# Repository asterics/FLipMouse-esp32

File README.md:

# FLipMouse goes ESP32

This repository contains the ongoing progress on the firmware for the FLipMouse version 3.
It will be API-compatible with FLipMouse v2, but with major improvements on speed (instead of one CortexM0 we will have a dual-core Tensilica and an additional CortexM0 for USB).

If you want to have a look at the FLipMouse v2, follow [this](https://github.com/asterics/FLipMouse) link to the main repository.

The BLE-HID stuff is based on the other [repository](https://github.com/asterics/esp32_mouse_keyboard), where we use the ESP32 as BLE module replacement.

Online demo version of Web GUI: https://asterics.github.io/FLipMouse-esp32/

__Following 3 steps are necessary to completely update/flash the firmware and the necessary support files/devices:__

## Building the ESP32 firmware

Please follow the step-by-step instructions of Espressif's ESP-IDF manual to setup the build infrastructure:
[Setup Toolchain](https://esp-idf.readthedocs.io/en/latest/get-started/index.html#setup-toolchain)

__Note:__ Due to frequent breaking changes within the esp-idf and all build tools, we recommend to use a specific version of the tools:
* release v4.1 (on 04.02.2020)
* master branch (on 04.02.2020)

To get this version, use the following commands:

  `git clone -b release/v4.1 --recursive https://github.com/espressif/esp-idf.git`  
  `cd esp-idf`  
  `./install.sh`  
  `. ./export.sh`  

																																																																																																																																																																																																																																																																																																																																																																																																																																																																																																																																																																																																																																																																																																																																																																																																																																																																																																																																																																																																																																																																																																																																																																																																																																																																																																																																																																																																																																																																																																																																																																																																																																																																																																																																																																																																																																																																																																																																																																																																																																																																																																																																																																																																												
__Now change your directory into the root directory of this repository.__

Create the sdkconfig:
* Execute `make menuconfig` in this directory
* Change: `Serial flasher config` -> `Flash size` to __4MB__
* Change: `Partition table` -> `Partition table` to __Custom partition table CSV__
* Change: `Component config` -> `Bluetooth` to enabled

Optional (for runtime statistics):
* Change: `Component config`->`FreeRTOS`->`Enable FreeRTOS trace facility` to enabled

Optional (extensive stack/heap debugging):
* Change `Component config`->`Heap memory debugging`->`Heap corruption detection` to whatever you need

After a successful setup, you should be able to build the FLipMouse/FABI firmware by executing 'make flash monitor'.

## Building the LPC11U14 firmware (USB bridging chip)

The dedicated USB chip firmware is located in this repository: [usb_bridge](https://github.com/benjaminaigner/usb_bridge/).
Please clone this repository, and import it into the MCUXpresso IDE.

You can download the IDE here:
[MCUXpresso IDE](http://www.nxp.com/mcuxpresso/ide)

After a successful build, you need to flash the firmware to the LPC11U14 chip. We recommend using a development board by Embedded Artists,
because it is very useful for initial testing & debugging. It is possible to split this board into two pieces, one LPC11U14 target and a JTAG
programmer, which we use on a fully assembled FLipMouse. Please refer to the corresponding documents of this board how to connect the JTAG header to
our FLipMouse (will be announced as soon as the PCB is final).

LPCXpresso development board:

[LPCXpresso 11U14](http://embeddedartists.com/products/lpcxpresso/lpc11U14_xpr.php)

## Uploading the WebGUI

The FLipMouse with ESP32 contains a web interface for customizing the parameters. The web page itself is located in the FAT partition as the config data.

-----------------------

TBA: I think it is very easy to use mkfats by copying the component into ESP-IDF and simply call **make mkfatfs** to build the tool and **make flashfatfs** to upload the image.

**BUT** we have a 8.3 naming convention here...

Currently proposed workflow:

-----------------------

Please clone/download the [mkfats](https://github.com/jkearins/ESP32_mkfatfs) tool, and copy the folder `ESP32_mkfatfs/components/mkfatfs` into your
ESP-IDF's components path.

Execute `make mkfatfs` in this repository to build the *mkfatfs* tool.

If you want to update the webpage on the FLipMouse/FABI device, execute:

`make makefatfs flashfatfs`

_WARNING:_** All your slot configuration and IR commands will be deleted by this operation.

## WARNING: THIS IS EARLY WORK IN PROGRESS

# Acknowledgements

Supporters, MA23, people using this device and many more for input.

ESP-IDF developers for HOG testcode

mkfatfs project

thanks to Luca Dentella for the esp32lights demo, see http://www.lucadentella.it/en/2018/01/08/esp32lights/

thanks to Jeroen Domburg and Cornelis for the captive portal DNS code, see: https://github.com/cornelis-61/esp32_Captdns

thanks to Thomas Barth for esp32 Websocket demo code, see https://github.com/ThomasBarth/WebSockets-on-the-ESP32/

thanks to Lucas Bruder for the Neopixel library for ESP32, see https://github.com/Lucas-Bruder/ESP32_LED_STRIP/

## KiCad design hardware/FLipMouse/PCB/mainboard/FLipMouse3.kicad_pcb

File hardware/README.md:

# FABI

This PCB is intended to be used with a **AK-S-01** case, produced by Szomk.

**Note:** This PCB was not produced yet, so no functional guarantee!

# FLipMouse 

This FLipMouse-esp32 PCB is tested by the *_PRE versions of the PCB.

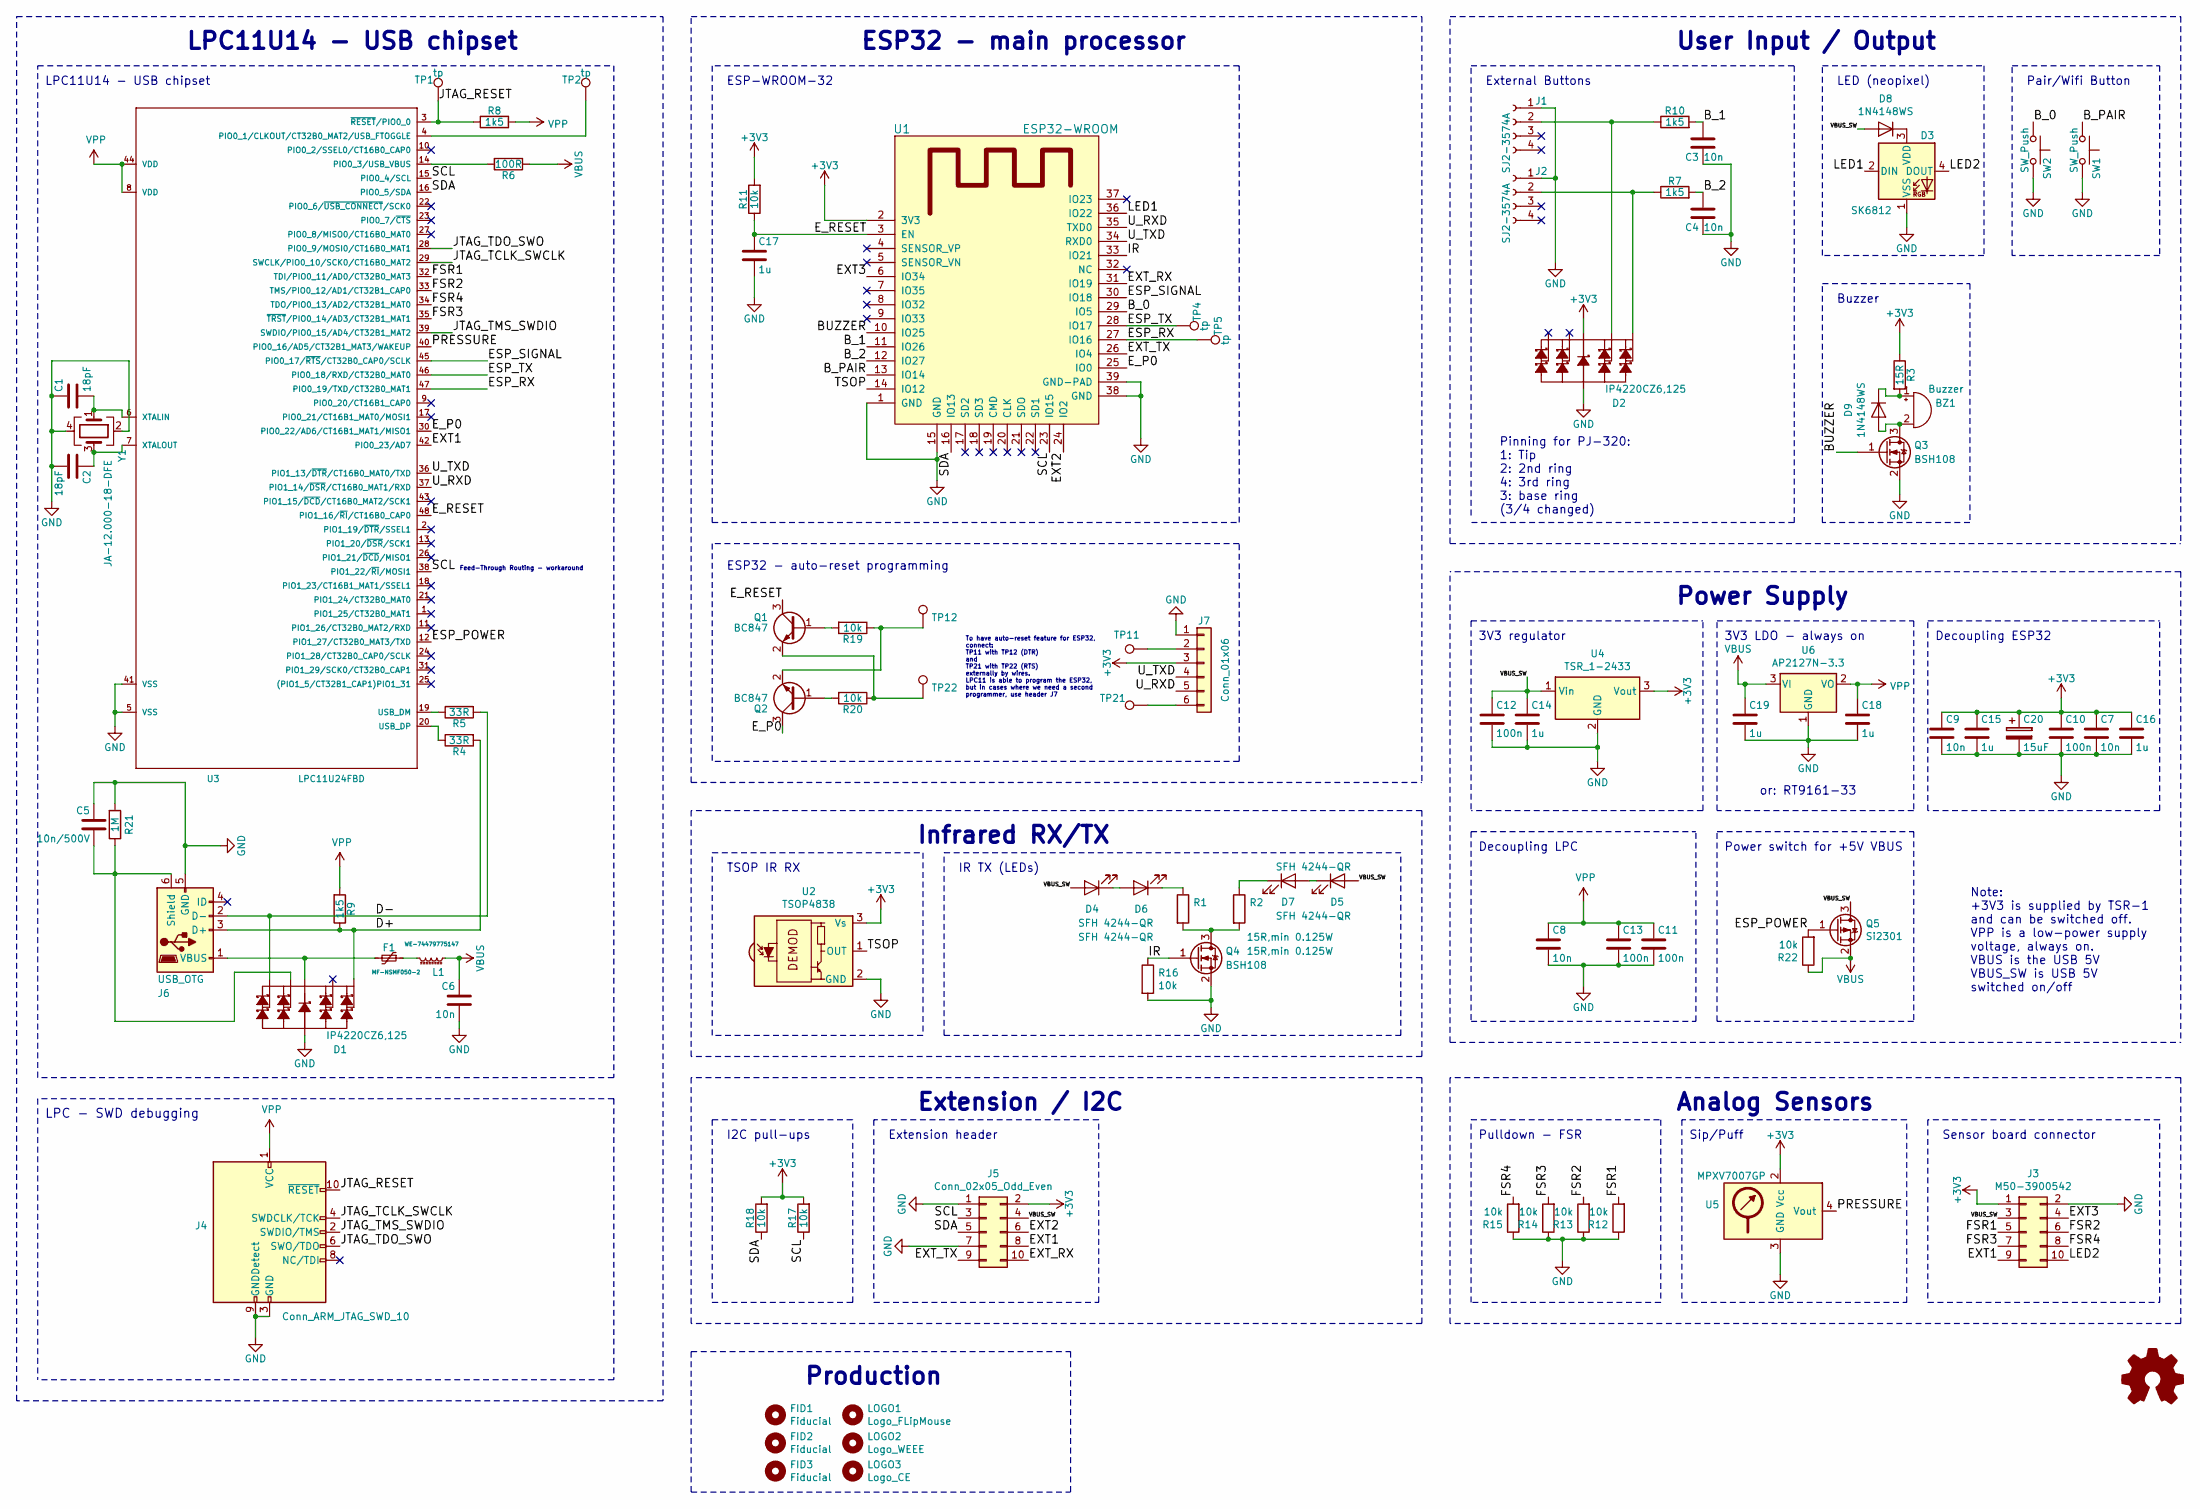
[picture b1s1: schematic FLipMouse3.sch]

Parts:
BZ1: Buzzer; MagneticBuzzer_Kingstate_KCG0601
C1, C2: 18pF; C_0603_1608Metric
C3, C4, C6, C7, C8, C9: 10n; C_0603_1608Metric
C5: 10n/500V; C_0603_1608Metric
C10, C11, C12, C13: 100n; C_0603_1608Metric
C14, C15, C16, C17, C18, C19: 1u; C_0805_2012Metric
C20: 15uF; CP_EIA-3216-18_Kemet-A
D1, D2: IP4220CZ6,125; SOT457
D3: SK6812; LED_SK6812_PLCC4_5.0x5.0mm_P3.2mm
D4, D5, D6, D7: SFH 4244-QR; SFH4244
D8, D9: 1N4148WS; D_SOD-323
F1: MF-NSMF050-2; C_1206_3216Metric
FID1, FID2, FID3: Fiducial; Fiducial_0.5mm_Dia_1mm_Outer
J1, J2: SJ2-3574A; Jack_3.5mm_SJ2-357X
J3: M50-3900542; PinHeader_2x05_P1.27mm_Horizontal
J4: Conn_ARM_JTAG_SWD_10; PinHeader_2x05_P1.27mm_Vertical_SMD
J5: Conn_02x05_Odd_Even; PinHeader_2x05_P1.27mm_Vertical_SMD
J6: USB_OTG; USB_Micro-B
J7: Conn_01x06; PinSocket_1x06_P1.27mm_Vertical
L1: WE-74479775147; L_0805_2012Metric
LOGO1: Logo_FLipMouse; flipmouse_11x5
LOGO2: Logo_WEEE; WEEE-Logo_4.2x6mm_SilkScreen
LOGO3: Logo_CE; CE
Q1, Q2: BC847; SOT-23
Q3, Q4: BSH108; SOT-23
Q5: Si2301; SOT-23
R1, R2: 15R,min 0.125W; R_0603_1608Metric
R3: 15R; R_0603_1608Metric
R4, R5: 33R; R_0603_1608Metric
R6: 100R; R_0603_1608Metric
R7, R8, R9, R10: 1k5; R_0603_1608Metric
R11, R12, R13, R14, R15, R16, R17, R18, R19, R20, R22: 10k; R_0603_1608Metric
R21: 1M; R_0603_1608Metric
SW1, SW2: SW_Push; SW_Tactile_SPST_Angled_PTS645Vx83-2LFS
TP1, TP2, TP4, TP5: tp; Measurement_Point_Round-SMD-Pad_Small
TP11, TP12, TP21, TP22: TP; TestPoint_Pad_D1.0mm
U1: ESP32-WROOM
U2: TSOP4838; Vishay_MOLD-3Pin
U3: LPC11U24FBD; LQFP-48_7x7mm_P0.5mm
U4: TSR_1-2433; Converter_DCDC_TRACO_TSR-1_THT
U5: MPXV7007GP
U6: AP2127N-3.3; SOT-23
Y1: JA-12.000-18-DFE; Crystal_SMD_3225-4Pin_3.2x2.5mm

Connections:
+3V3: C7.1, C9.1, C10.1, C15.1, C16.1, C20.1, D2.5 (VCC), J3.1, J5.2, J7.3, R3.1, R11.2, R17.2, R18.2, U1.2 (3V3), U2.3 (Vs), U4.3 (Vout), U5.2 (Vcc)
/BUZZER: Q3.1 (G), U1.10 (IO25)
/B_0: SW2.1, U1.29 (IO5)
/B_1: C3.2, R10.2, U1.11 (IO26)
/B_2: C4.2, R7.2, U1.12 (IO27)
/B_PAIR: SW1.1, U1.13 (IO14)
/D+: D1.6 (IO), J6.3 (D+), R4.2, R9.1
/D-: D1.1 (IO), J6.2 (D-), R5.2
/ESP_POWER: Q5.1 (G), R22.2, U3.12 (PIO1_27/CT32B0_MAT3/TXD)
/ESP_RX: TP5.1, U1.27 (IO16), U3.47 (PIO0_19/TXD/CT32B0_MAT1)
/ESP_SIGNAL: U1.30 (IO18), U3.45 (PIO0_17/~RTS~/CT32B0_CAP0/SCLK)
/ESP_TX: TP4.1, U1.28 (IO17), U3.46 (PIO0_18/RXD/CT32B0_MAT0)
/EXT1: J3.9, J5.8, U3.42 (PIO0_23/AD7)
/EXT2: J5.6, U1.24 (IO2)
/EXT3: J3.4, U1.6 (IO34)
/EXT_RX: J5.10, U1.31 (IO19)
/EXT_TX: J5.9, U1.26 (IO4)
/E_P0: Q2.3 (C), U1.25 (IO0), U3.30 (PIO0_22/AD6/CT16B1_MAT1/MISO1)
/E_RESET: C17.1, Q1.3 (C), R11.1, U1.3 (EN), U3.48 (PIO1_16/~RI~/CT16B0_CAP0)
/FSR1: J3.5, R12.2, U3.32 (TDI/PIO0_11/AD0/CT32B0_MAT3)
/FSR2: J3.6, R13.2, U3.33 (TMS/PIO0_12/AD1/CT32B1_CAP0)
/FSR3: J3.7, R14.2, U3.35 (~TRST~/PIO0_14/AD3/CT32B1_MAT1)
/FSR4: J3.8, R15.2, U3.34 (TDO/PIO0_13/AD2/CT32B1_MAT0)
/IR: Q4.1 (G), R16.1, U1.33 (IO21)
/JTAG_RESET: J4.10 (~RESET~), R8.1, TP1.1, U3.3 (~RESET~/PIO0_0)
/JTAG_TCLK_SWCLK: J4.4 (SWDCLK/TCK), U3.29 (SWCLK/PIO0_10/SCK0/CT16B0_MAT2)
/JTAG_TDO_SWO: J4.6 (SWO/TDO), U3.28 (PIO0_9/MOSI0/CT16B0_MAT1)
/JTAG_TMS_SWDIO: J4.2 (SWDIO/TMS), U3.39 (SWDIO/PIO0_15/AD4/CT32B1_MAT2)
/LED1: D3.2 (DIN), U1.36 (IO22)
/LED2: D3.4 (DOUT), J3.10
/PRESSURE: U3.40 (PIO0_16/AD5/CT32B1_MAT3/WAKEUP), U5.4 (Vout)
/SCL: J5.3, R17.1, U1.23 (IO15), U3.15 (PIO0_4/SCL), U3.38 (PIO1_22/~RI~/MOSI1)
/SDA: J5.5, R18.1, U1.16 (IO13), U3.16 (PIO0_5/SDA)
/TSOP: U1.14 (IO12), U2.1 (OUT)
/U_RXD: J7.5, U1.35 (TXD0), U3.37 (PIO1_14/~DSR~/CT16B0_MAT1/RXD)
/U_TXD: J7.4, U1.34 (RXD0), U3.36 (PIO1_13/~DTR~/CT16B0_MAT0/TXD)
/VBUS_SW: C12.1, C14.1, D4.2 (A), D5.2 (A), D8.2 (A), J3.3, J5.4, Q5.3 (D), U4.1 (Vin)
GND: C1.1, C2.2, C3.1, C4.1, C5.1, C6.2, C7.2, C8.2, C9.2, C10.2, C11.2, C12.2, C13.2, C14.2, C15.2, C16.2, C17.2, C18.2, C19.2, C20.2, D1.2 (GND), D2.2 (GND), D3.1 (VSS), J1.1, J2.1, J3.2, J4.3 (GND), J4.5 (GND), J4.9 (GNDDetect), J5.1, J5.7, J6.5 (GND), J7.1, Q3.2 (S), Q4.2 (S), R12.1, R13.1, R14.1, R15.1, R16.2, R21.2, SW1.2, SW2.2, U1.1 (GND), U1.15 (GND), U1.38 (GND), U1.39 (GND-PAD), U2.2 (GND), U3.5 (VSS), U3.41 (VSS), U4.2 (GND), U5.3 (GND), U6.1 (GND), Y1.2, Y1.4
unnamed: BZ1.1 (-), D9.1 (K), R3.2
unnamed: BZ1.2 (+), D9.2 (A), Q3.3 (D)
unnamed: C1.2, U3.6 (XTALIN), Y1.1
unnamed: C2.1, U3.7 (XTALOUT), Y1.3
unnamed: C5.2, D1.3 (IO), J6.6 (Shield), R21.1
unnamed: D1.5 (VCC), F1.2, J6.1 (VBUS)
unnamed: D2.4 (IO), J1.2, R10.1
unnamed: D2.6 (IO), J2.2, R7.1
unnamed: D3.3 (VDD), D8.1 (K)
unnamed: D4.1 (K), D6.2 (A)
unnamed: D5.1 (K), D7.2 (A)
unnamed: D6.1 (K), R1.1
unnamed: D7.1 (K), R2.1
unnamed: F1.1, L1.1
unnamed: J7.2, TP11.1
unnamed: J7.6, TP21.1
unnamed: Q1.1 (B), R19.2
unnamed: Q1.2 (E), R20.1, TP22.1
unnamed: Q2.1 (B), R20.2
unnamed: Q2.2 (E), R19.1, TP12.1
unnamed: Q4.3 (D), R1.2, R2.2
unnamed: R4.1, U3.20 (USB_DP)
unnamed: R5.1, U3.19 (USB_DM)
unnamed: R6.2, U3.14 (PIO0_3/USB_VBUS)
unnamed: TP2.1, U3.4 (PIO0_1/CLKOUT/CT32B0_MAT2/USB_FTOGGLE)
VBUS: C6.1, C19.1, L1.2, Q5.2 (S), R6.1, R22.1, U6.3 (VI)
VPP: C8.1, C11.1, C13.1, C18.1, J4.1 (VCC), R8.2, R9.2, U3.8 (VDD), U3.44 (VDD), U6.2 (VO)

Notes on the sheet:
Pair/Wifi Button
Buzzer
LED (neopixel)
Pinning for PJ-320: 1: Tip 2: 2nd ring 4: 3rd ring 3: base ring (3/4 changed)
LPC11U14 - USB chipset
Decoupling ESP32
External Buttons
ESP32 - auto-reset programming
LPC - SWD debugging
ESP-WROOM-32
User Input / Output
Power Supply
3V3 regulator
Decoupling LPC
Analog Sensors
Pulldown - FSR
Sip/Puff
Sensor board connector
Extension / I2C
I2C pull-ups
Extension header
ESP32 - main processor
Infrared RX/TX
TSOP IR RX
IR TX (LEDs)
Production
To have auto-reset feature for ESP32, connect: TP11 with TP12 (DTR) and TP21 with TP22 (RTS) externally by wires. LPC11 is able to program the ESP32, but in cases where we need a second programmer, use header J7
Feed-Through Routing - workaround
Note: +3V3 is supplied by TSR-1 and can be switched off. VPP is a low-power supply voltage, always on. VBUS is the USB 5V VBUS_SW is USB 5V switched on/off
or: RT9161-33
3V3 LDO - always on
Power switch for +5V VBUS

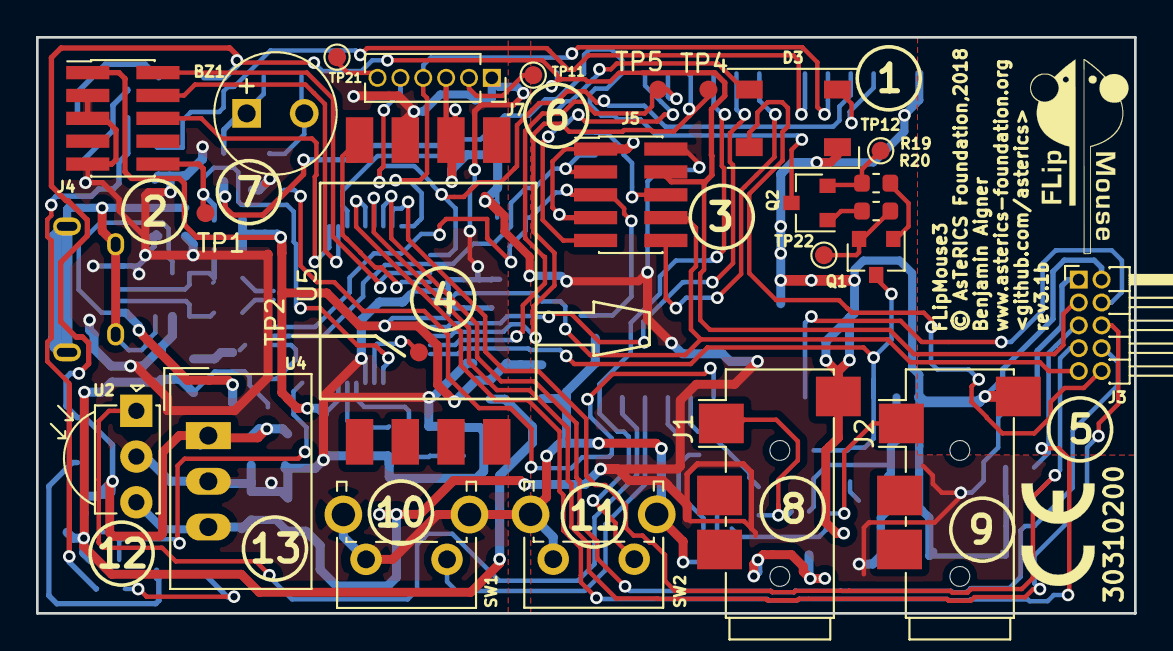
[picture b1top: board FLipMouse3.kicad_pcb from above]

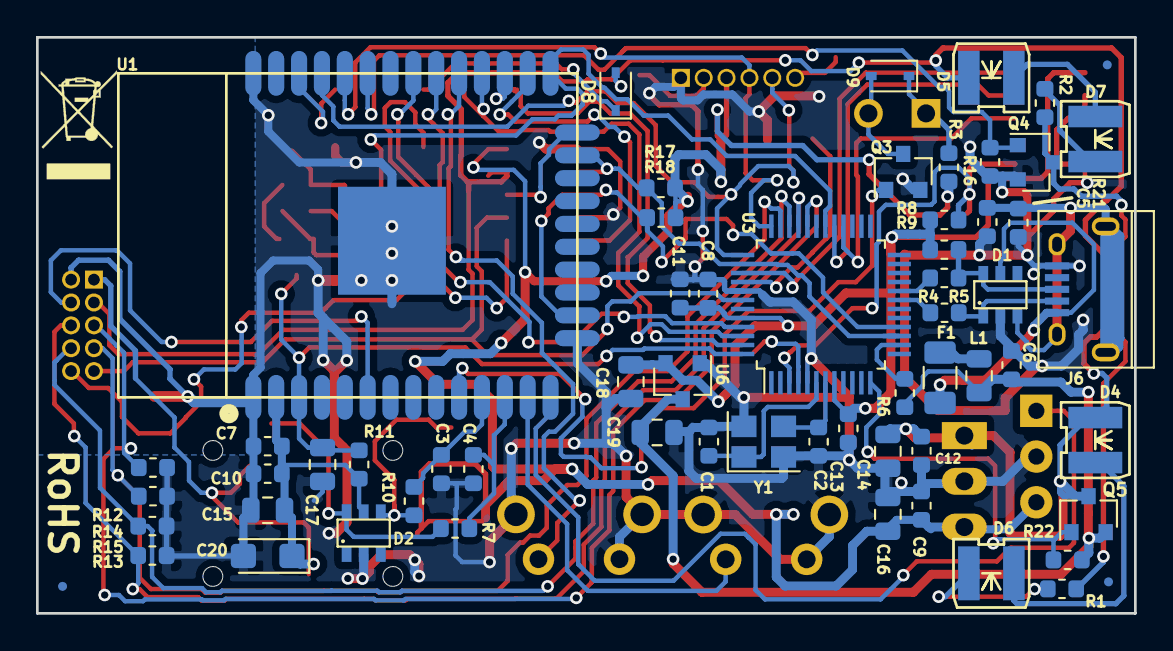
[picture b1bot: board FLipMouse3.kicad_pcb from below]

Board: 2 copper layers, 61.0 x 32.0 mm, 89 parts (62 on the bottom side), 65 nets.

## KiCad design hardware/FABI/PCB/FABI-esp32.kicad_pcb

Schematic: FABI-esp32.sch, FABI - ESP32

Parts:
BZ1: Buzzer; MagneticBuzzer_Kingstate_KCG0601
C1, C2: 18pF; C_0603_1608Metric
C3, C4, C5, C6, C7, C8, C9, C10, C12, C13, C14: 10n; C_0603_1608Metric
C11: 10n/500V; C_0603_1608Metric
C15, C16, C17, C18: 100n; C_0603_1608Metric
C19, C20, C21, C22: 1u; C_0805_2012Metric
C23: 15uF; CP_EIA-3216-18_Kemet-A
D1, D2, D3, D4: IP4220CZ6,125; SOT457
D5: 1N4148WS; D_SOD-323
D6: SK6812; LED_SK6812_PLCC4_5.0x5.0mm_P3.2mm
F1: MF-NSMF050-2; C_1206_3216Metric
FID1, FID2, FID3: Fiducial; Fiducial_0.5mm_Dia_1mm_Outer
J1, J2, J3, J4, J5, J6, J7, J8: SJ2-3574A; Jack_3.5mm_SJ2-357X
J9: USB_OTG; USB_Micro-B
J10: Conn_01x04; PinSocket_1x04_P2.54mm_Vertical
J11: Conn_01x06; PinHeader_1x06_P2.54mm_Vertical
J12: Conn_01x08_Male; PinHeader_1x08_P2.54mm_Vertical
J13, J14, J15, J16, J17: tp; TestPoint_Pad_D1.0mm
L1: WE-74479775147; L_0805_2012Metric
LOGO1: LOGO_CE; CE
LOGO2, LOGO4: LOGO_FABI; fabi_15x8
LOGO3: LOGO_WEEE; WEEE-Logo_4.2x6mm_SilkScreen
MH1, MH2, MH3, MH4: TEST; MountingHole_4.5mm_wo_crtyd
Q1, Q2: BC847; SOT-23
Q3, Q4, Q5: BSH108; SOT-23
R1, R2: 33R; R_0603_1608Metric
R3, R4: 100R; R_0603_1608Metric
R5, R6, R7, R8, R9, R10, R14: 1.5k; R_0603_1608Metric
R11, R12, R13: 1k5; R_0603_1608Metric
R15, R16, R17, R18, R19, R20: 10k; R_0603_1608Metric
R21: 1M; R_0603_1608Metric
SW1: SW_Push; SW_Tactile_SPST_Angled_PTS645Vx83-2LFS
U1: ESP32-WROOM
U2: TSR_1-2433; Converter_DCDC_TRACO_TSR-1_THT
U3: LPC11U14FBD; LQFP-48_7x7mm_P0.5mm
Y1: JA-12.000-18-DFE; Crystal_SMD_3225-4Pin_3.2x2.5mm

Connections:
+3V3: C12.1, C13.1, C14.1, C15.1, C16.1, C17.1, C19.1, C22.1, C23.1, D1.5 (VCC), D2.5 (VCC), D3.4 (IO), D3.5 (VCC), J8.2, J10.2, J11.3, J12.1, R11.1, R12.2, R13.2, R17.2, R18.2, R20.2, U1.2 (3V3), U2.3 (Vout), U3.8 (VDD), U3.44 (VDD)
/BUZZER: Q3.1 (G), U1.12 (IO27)
/B_0: C6.2, R14.2, U1.4 (SENSOR_VP)
/B_1: C8.2, R8.2, U1.5 (SENSOR_VN)
/B_2: C3.2, R5.2, U1.8 (IO32)
/B_3: C4.2, R6.2, U1.9 (IO33)
/B_4: C5.2, R7.2, U1.10 (IO25)
/B_5: C7.2, R9.2, U1.11 (IO26)
/B_6: C9.2, R10.2, U1.13 (IO14)
/B_PAIR: SW1.1, U1.37 (IO23)
/D+: D4.6 (IO), J9.3 (D+), R2.2, R13.1
/D-: D4.1 (IO), J9.2 (D-), R1.2
/DD+: R2.1, U3.20 (USB_DP)
/DD-: R1.1, U3.19 (USB_DM)
/ESP_POWER: Q5.1 (G), U3.27 (PIO0_8/MISO0/CT16B0_MAT0)
/ESP_RX: J17.1, U1.27 (IO16), U3.47 (PIO0_19/TXD/CT32B0_MAT1)
/ESP_SIGNAL: U1.30 (IO18), U3.45 (PIO0_17/~RTS~/CT32B0_CAP0/SCLK)
/ESP_TX: J16.1, U1.28 (IO17), U3.46 (PIO0_18/RXD/CT32B0_MAT0)
/E_P0: Q2.3 (C), U1.25 (IO0)
/E_RESET: C21.1, Q1.3 (C), R20.1, U1.3 (EN)
/IR: Q4.1 (G), R15.2, U1.31 (IO19)
/JTAG_RESET: J12.6, J13.1, R12.1, U3.3 (~RESET~/PIO0_0)
/JTAG_TCLK_SWCLK: J12.3, U3.29 (SWCLK/PIO0_10/SCK0/CT16B0_MAT2)
/JTAG_TDO_SWO: J12.4, U3.28 (PIO0_9/MOSI0/CT16B0_MAT1)
/JTAG_TMS_SWDIO: J12.2, U3.39 (SWDIO/PIO0_15/AD4/CT32B1_MAT2)
/LED1: D6.2 (DIN), U1.36 (IO22)
/SCL: J10.4, R18.1, U1.23 (IO15), U3.15 (PIO0_4/SCL)
/SDA: J10.3, R17.1, U1.16 (IO13), U3.16 (PIO0_5/SDA)
/TSOP: R4.1, U1.7 (IO35)
/U_RXD: J11.5, U1.35 (TXD0)
/U_TXD: J11.4, U1.34 (RXD0)
GND: C1.1, C2.2, C10.2, C11.1, C13.2, C14.2, C15.2, C16.2, C18.2, C19.2, C20.2, D4.2 (GND), J9.5 (GND), J12.8, Q5.2 (S), R21.2, U2.2 (GND), U3.5 (VSS), U3.41 (VSS), Y1.2, Y1.4
GNDD: C3.1, C4.1, C5.1, C6.1, C7.1, C8.1, C9.1, C12.2, C17.2, C21.2, C22.2, C23.2, D1.2 (GND), D2.1 (IO), D2.2 (GND), D3.2 (GND), D3.3 (IO), D6.1 (VSS), J1.1, J2.1, J3.1, J4.1, J5.1, J6.1, J7.1, J8.4, J10.1, J11.1, Q3.2 (S), Q4.2 (S), Q5.3 (D), R15.1, SW1.2, U1.1 (GND), U1.15 (GND), U1.38 (GND), U1.39 (GND-PAD)
unnamed: BZ1.1 (-), R11.2
unnamed: BZ1.2 (+), Q3.3 (D)
unnamed: C1.2, U3.6 (XTALIN), Y1.1
unnamed: C2.1, U3.7 (XTALOUT), Y1.3
unnamed: C11.2, D4.4 (IO), J9.6 (Shield), R21.1
unnamed: D1.1 (IO), J3.2, R5.1
unnamed: D1.3 (IO), J4.2, R6.1
unnamed: D1.4 (IO), J2.2, R8.1
unnamed: D1.6 (IO), J1.2, R14.1
unnamed: D2.3 (IO), J7.2, R10.1
unnamed: D2.4 (IO), J6.2, R9.1
unnamed: D2.6 (IO), J5.2, R7.1
unnamed: D3.1 (IO), J8.3, Q4.3 (D)
unnamed: D3.6 (IO), J8.1, R4.2
unnamed: D4.5 (VCC), F1.2, J9.1 (VBUS)
unnamed: D5.1 (K), D6.3 (VDD)
unnamed: F1.1, L1.1
unnamed: J11.2, Q2.2 (E), R19.1
unnamed: J11.6, Q1.2 (E), R16.1
unnamed: J14.1, U3.4 (PIO0_1/CLKOUT/CT32B0_MAT2/USB_FTOGGLE)
unnamed: J15.1, R3.2, U3.14 (PIO0_3/USB_VBUS)
unnamed: Q1.1 (B), R19.2
unnamed: Q2.1 (B), R16.2
VBUS: C10.1, C18.1, C20.1, D5.2 (A), L1.2, R3.1, U2.1 (Vin)

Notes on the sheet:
Pair/Wifi Button
Buzzer
LED (neopixel)
LPC11U14 - USB chipset
Decoupling for LPC & ESP32
IR+TSOP external Jackplug
7x external Jackplugs
3V3 regulator + power switch for ESP32
Designed like ESP32 Thing (Sparkfun)
Programming interfaces
ESP-WROOM-32
I2C (display or ext)
Mounting holes
Note: to have 3v3 compatible SK6812, we need to reduce the supply voltage: 5V-0,7V->4,3V*0,7->Din(high,min) = 3V
Microcontrollers
User I/O
Power
Production
Infrared (external)
USB compatible interface
Logos
Fiducials

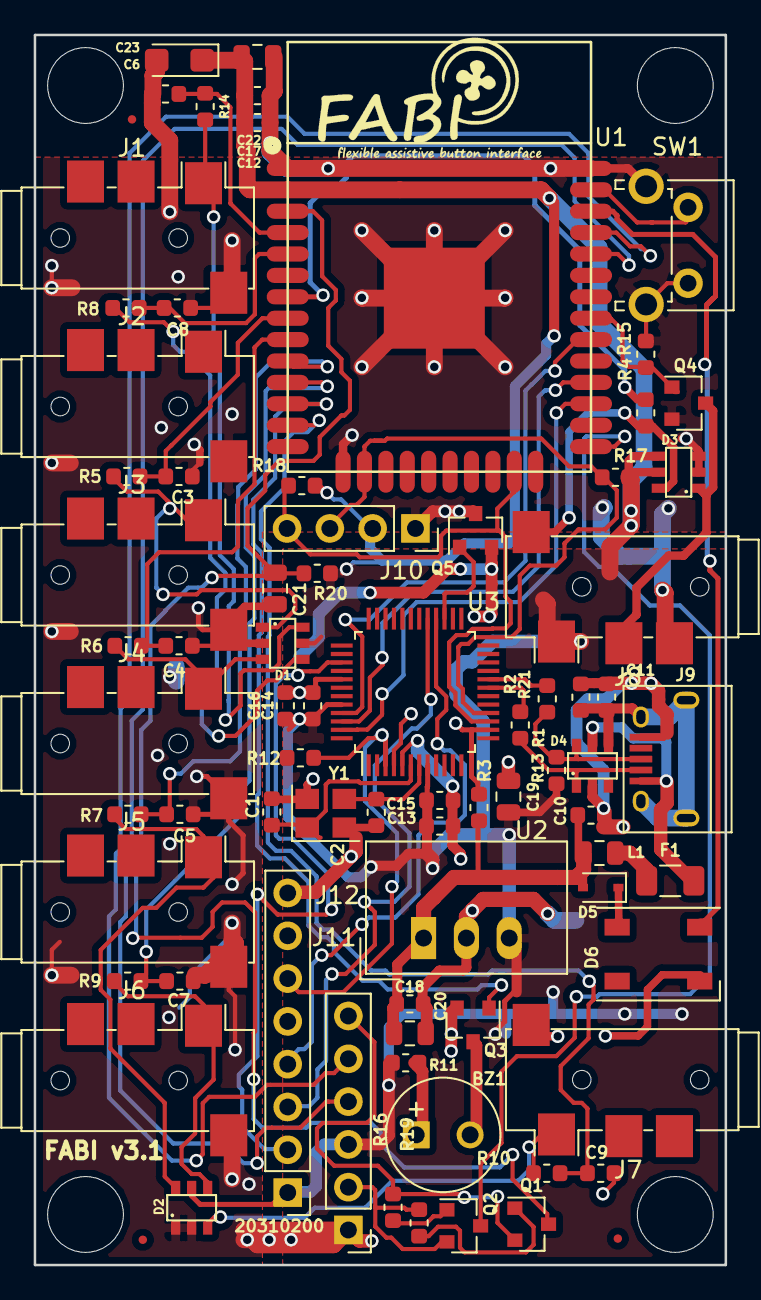
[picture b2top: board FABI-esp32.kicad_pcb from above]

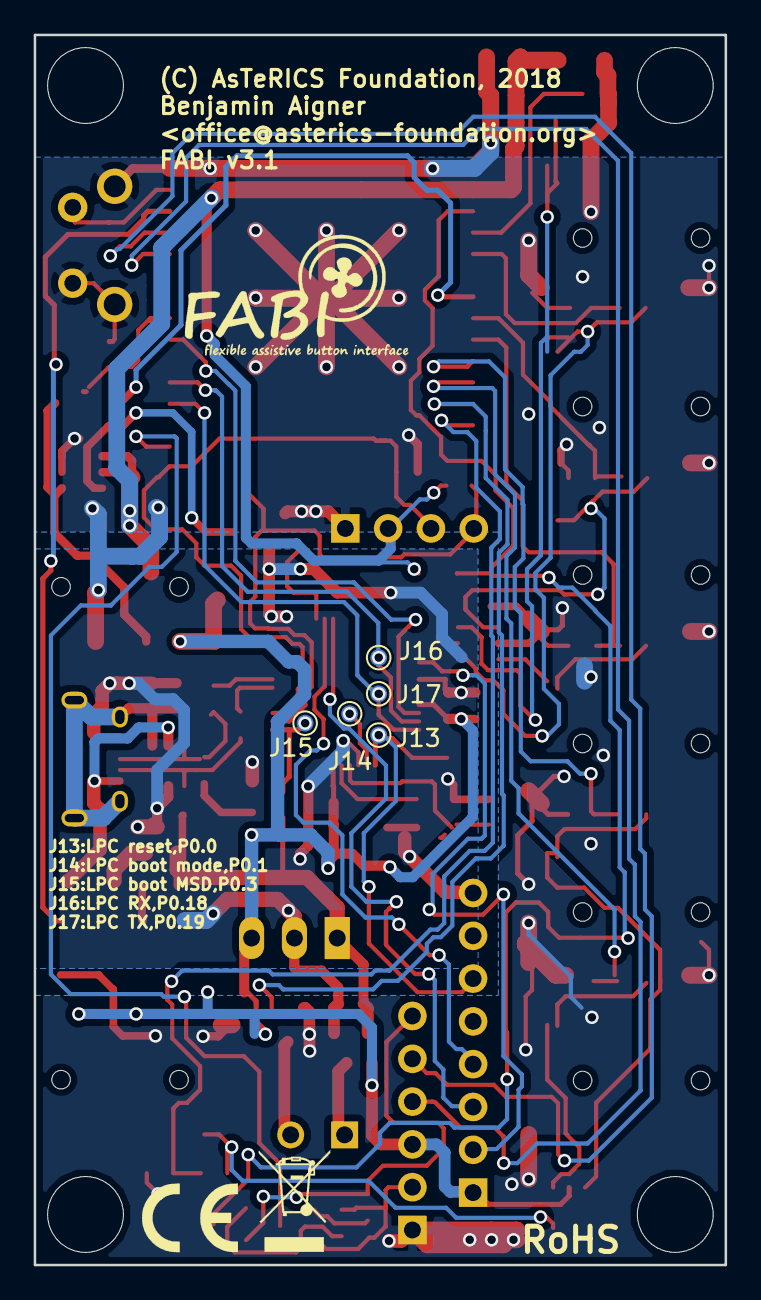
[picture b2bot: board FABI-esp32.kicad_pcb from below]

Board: 2 copper layers, 41.0 x 73.0 mm, 91 parts (8 on the bottom side), 57 nets.

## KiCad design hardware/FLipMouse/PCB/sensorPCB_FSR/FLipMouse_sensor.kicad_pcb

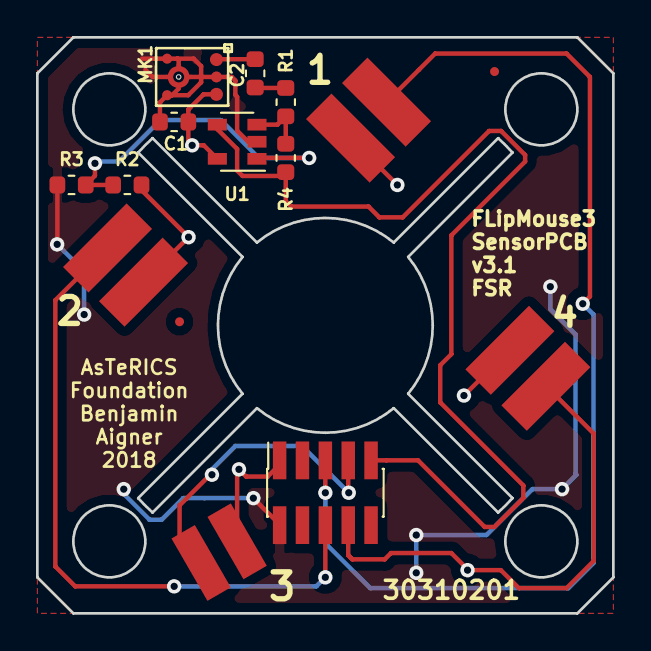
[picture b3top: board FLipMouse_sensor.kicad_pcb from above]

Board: 2 copper layers, 32.0 x 32.0 mm, 19 parts (0 on the bottom side), 11 nets.

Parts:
C1: 100nF; C_0603_1608Metric
C2: 4.7uF; C_0603_1608Metric
FID1, FID2: Fiducial; Fiducial_0.5mm_Dia_1mm_Outer
J1: Conn_02x05_Odd_Even; PinSocket_2x05_P1.27mm_Vertical_SMD
J2, J3: FSR1; FSRPAD
J4, J5: FSR2; FSRPAD
J6, J7: FSR3; FSRPAD
J8, J9: FSR4; FSRPAD
MK1: SPU0410LR5H; SPU0410LR5H_6_3.76x3mm
R1: 10k; R_0603_1608Metric
R2, R3, R4: 100k; R_0603_1608Metric
U1: LMV321; SOT-23-5

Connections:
3V3: C1.1, J1.1, J3.1, J5.1, J7.1, J9.1, MK1.4, R2.2, U1.5
/1: J1.5, J2.1
/2: J1.6, J4.1
/3: J1.7, J6.1
/4: J1.8, J8.1
/EXT1: J1.9, R4.1, U1.4
GNDD: C1.2, J1.2, MK1.2, MK1.3, MK1.5, MK1.6, R3.1, U1.2
unnamed: C2.1, R1.2
unnamed: C2.2, MK1.1
unnamed: R1.1, R4.2, U1.3
unnamed: R2.1, R3.2, U1.1

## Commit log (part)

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2018-05-03 changed colors in order to meet aria contrast criteria
2018-05-03 added translations for "connected" and "not connected"
2018-05-03 added classes for displaying items only for screenreaders and for connection indicators
2018-05-04 changed access keys of sip/puff sliders because alt+e is chrome menu
2018-05-06 Added mode for strong sip/puff
2018-05-06 Added conditions for strong mode + XX in tasks, handling tbd
2018-05-09 Reduced priority of tasks for kbd/mouse/joystick & set baudrate to 115200
2018-05-12 Added a check for current BT status, avoiding errors on re-enabling
2018-05-12 Added compatibility flag
2018-05-12 Starting with slot number 0, not having a "special", not removable slot.
2018-05-12 Added v2.5. note on AT LA/ AT DE
2018-05-12 Put LED update into the macro instead of a task (Neopixel still need a task)
2018-05-16 Fixed heap corruption with reduced buffers
2018-05-21 Changed task priority of config switcher, removed NL characters from ID string
2018-05-21 Added opening partition, to be save if webgui is initialized before storage
2018-05-21 Starting with slot 0, no "DEFAULT" slot
2018-05-21 Changed RMT blocks to 3, on all occasions, freeing one for Neopixels and one for HID output
2018-05-22 Added declaration for queue & usb command
2018-05-23 Added note on slot 0
2018-05-23 Changed for new HID sending
2018-05-23 Added "END" after sending a slot
2018-05-23 Changed storage for slot 0 and -1 for delete all, added note. AT LA bugfix, sending "END" at the end
2018-05-24 Updated documentation & changed loglevel for USB mouse to DEBUG
2018-05-24 Fixed corrupted slots on save due to not-synchronized config data
2018-05-24 Extended data output for saving slots (deactivated by #if 0)
2018-05-28 Removed espressif BLE stuff, added Nkolban's BLE stack
2018-05-28 Improved&simplified calibration:
    - Using same adc read function
    - Removing problem with sensor gain (was not take into account for calibration)
2018-05-28 implemented queue parsing
2018-05-28 BLE/WiFi switch without pairing (is normally active if no device is connected)
2018-05-28 Changed AT BM numbering
2018-05-29 Added sip/puff calibration. Sometimes the 5V type has a significant offset, is calibrated now
2018-05-29 Reduced debug output, controllable via LOG_LEVEL_STORAGE define
2018-05-29 Moved radio switch to main task, reducing stack load on timer
2018-05-29 Reduced main stack size, fixed error on switching off wifi
2018-05-30 Changed stacksize to 8k, replaced printf by ESP_LOGx
2018-05-30 Activated BT/Wifi coexistance, don't know if it helps...
2018-06-04 Changed error checks for getting wifi station count, added guards for wifi deinit
2018-06-04 Doxygen docs updated to current status
2018-06-13 Changed individual tasks to task_hid
2018-06-13 Added HID task
2018-06-13 Added store/load for HID command chain
2018-06-13 Rewrote parser for short HID commands
2018-06-21 Removed now unused kbd/mouse tasks -> moved to task_hid
2018-06-21 Changed comments -> HID task is continous, not functional.
2018-06-21 Changed further to use simple VB task
2018-07-24 Changed sdkconfig & websocket file for esp-idf release v3.1
2018-08-03 Renamed default file to flip.set (allowing a default fabi.set)
2018-08-06 Changed load function to use AT commands from files.
2018-08-07 Major improvements/fixes:
    - Fixed AT AY command
    - Fixing buffer errors on AT SS/AT SP
    - Moved slot storing to an individual function (refactored old printAll function -> now storing AT commands in flash)
    - Slot printing is now mostly done in hal_storage (because the output of "AT LA" is already stored in flash)
2018-08-07 Major improvements:
    - Added a stripping function to remove \r\n
    - Changed config names from 000.fms to 000.set
    - Added serial output to halStorageLoadNumber -> replacing the printAll function from task_commands
    - Added a global file handle for a session, allow appending lines on each call of halStorageStore (less memory for saving AT command lines)
    - Removed all VB/HID chain store/load functions
2018-08-07 Implemented "AT NE" by sending command chain parameter to config switcher queue
2018-08-07 Added breaks for command type detection
2018-08-13 DOXY: Typos, Todos
2018-08-14 OTF calibration, not activated now (missing good values from normal sensors)
2018-10-10 Changed component names for having all part types in one order. Added 3d shapes & beautified silkscreen layers.
2018-10-15 Added requirementsspecification for FABI3 (necessary for certification)
2018-11-15 Production ready, alpha: * Added marks/logos/fiducials * Changed neopixel driving * Moved RX/TX of EXT header from internal UART to free pins * Renumbered all parts for having same part types with fo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
2018-11-21 Checklist: removed EdgeCut layer from single page PCB print Added the update of the 3D renderings
2018-11-21 Improvements&fixes: * Replaced PJ320D (china jack plugs) with plugs from digikey (RoHS!) * Added remaining 3D shapes to PCB * Removed GND from unused jack plug pins (might result in unusable buttons 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
2018-11-25 Pin config update for FABI, removed OTF calibration via defines for FABI
2018-11-25 Added kicad backup files to gitignore, added FABI rescue lib
2018-12-02 Updated FLipMouse PCB: - Routed ADC inputs (FSR+pressure) to LPC11 too (in case of crappy ESP ADC values) - Added ESP32 auto-reset pins to LPC11 (enabling programming via LPC USB) - Cleanup regarding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
2019-01-07 Added function to check if 'sip and puff' is available
2019-01-29 Added default files for FLipMouse configs. Removed gain settings
2019-01-29 Small documentation updates. Fixed R10, according to batch documentation (batch 'a'), from 1k5 to 15R (series resistor for buzzer)
2019-02-05 Clearing empty command queue flag before loading slots. Changed debug level to info
2019-02-05 Changed to use new parser:
    -) Commands are defined now in structure
    -) Parser is based on: https://gitlab.com/ba.1150/cmd_parser_esp32
    -) Parser modifies either the generalConfig_t struct OR calls a handler
2019-02-05 Changed LED number if WiFi is active (now it is purple)
2019-02-05 Added debug output for command chain.
2019-02-05 remove newline
2019-02-06 Keycode parser using parameter, not full string. Added debug output for press action.
2019-02-07 Changed version string to v2.7 (compatible with FlipMouseGUI)
2019-02-08 Updated sdkconfig to esp idf release v3.2
2019-02-08 Changed wifi/ble switching: -) BLE is always active -) BLE/Wifi co-existance is done in esp-idf -) Wifi is switched on/off by the special button handler
2019-02-09 Added detailed debouncer output; added printf macros for printing single bits
2019-02-09 Replaced the out event flags (signalling to task_hid, task_vb) by an event loop:
    -) renamed task_hid / task_vb to handler_hid/handler_vb
    -) Deleted virtualButtonsOut event group
    -) Removed task structure, replaced by event handler
    -) Changed functions in all calling modules
2019-02-12 Fixed wrong IR file numbering -> could play, delete but not storing more than one IR command.
2019-02-13 Debouncer has highest priority.
2019-02-13 Fixed AT K* commands: press/release flags were wrong Cleaned up deboug output
2019-02-13 Fixed wrong press/release assignment for keyboard actions; removed trailing \r\n characters
2019-02-13 Fixed check for slot number (do this only on creating a new slot)
2019-03-08 Small comment updates; changed default slot settings
2019-03-11 ADC measurements via LPC - I2C communication for data
2019-03-11 Unified 3V3 (switched), according to chapter 9.4 of LPC datasheet, the high power pin doesn't deliver 3v3.
2019-03-13 Added an output for parsing errors.
2019-03-13 Changed log output to level info
2019-03-13 Changed SPIFFS script, modified sdkconfig to use same SPIFFS settings as mkspiffs in standard configuration
2019-03-15 UPdates in tone creation, queue was too short for e.g. slot nr 5 beeps.
2019-03-15 Disabled elliptic deadzone, can be enabled by define
2019-03-15 Fixed missing X+Y axis mouse command (was only active for a single axis).
2019-03-18 Moved BLE/Wifi init to the end with a delay
2019-03-20 Doxygen updates, resetting mouse wheel size to 3 if not set.
2019-03-22 Masked out press/release flag for getting active VBs
2019-03-22 Implemented strong sip/puff + additional action, cleaned up ADC code, removed ESP32's ADC init (unused)
2019-03-22 Doxygen - pulled to current source
2019-04-02 Updated PCB, final changes & refinements for v3.1b
2019-05-28 Improved error handling on spurious unusable sensor readings
2019-05-28 Improved web server handling:
    -) Tasks are correctly deleted after wifi disable
    -) Wifi can be enabled only once each power cycle
2019-07-04 Fixed restore defaults in webgui, done via "AT DE" followed by "AT LA"
2019-07-04 Added a partition table for OTA setup, see: https://github.com/asterics/esp32-uart-ota
2019-07-04 Updated doxygen docs
2019-07-10 Finalized MQTT. Working now in station mode, possible to add it on a VB
2019-07-10 added numbering details in hal_storage get slot number, fixed color error when wifi softap is deactivated
2019-07-11 Temporary commit, not buildable
2019-07-11 Added AT MQ & AT RE (MQTT & REST calls) as possible button actions to webgui
2019-07-17 made menubutton display flex -> everytime same height; added new tab "global config"
2019-07-18 added possibility to pass style to createElement
2019-07-18 added ID to spacer to be able to show/hide in javascript
2019-07-18 added possibility to define maximum timeout to resolve, if no result was received
2019-07-18 filled global properties tab
2019-07-18 changed AT IL lineending to \r\n
2019-07-19 Documented LED color on Wifi SoftAP activation
2019-07-19 Modified Websocket helper to support 16bits & 64bits payload length fields. UNTESTED
2019-07-19 Added output of general settings (AT MH, AT WH, AT ML)
2019-07-19 added node_modules to gitignore
2019-07-19 Added note on http URL length, added cleanup and check for active SoftAP wifi
2019-07-22 updated FABI webgui with changes from FlipMouse, harmonized code structure in tabact.js
2019-07-22 remember inital result of "isSipAndPuffLive" and reuse it
2019-07-22 added minified and gzipped versions of FABI and FLipmouse sources
2019-07-31 Added script for auto-generating a new webGUI image (SPIFFS)
2019-11-09 Working serial port interface, hardcoded USB IF!
2019-11-12 Fixed memory leak (with many action handlers in promise), fixed the wind-up of concat return data.
2019-12-05 With promises for port open
2019-12-06 Added the correct value handlers
2020-02-04 Updates for newer esp-idf (release v4 or todays master): -) removed unused variable of hal_ble -) changed wifi_get_reason to esp_err_to_name -) Added a guard macro for task statistics -) Changed base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
2020-03-23 Closing serial port if not successful, fixed a typo
2020-03-23 Added sloat loading, depending on running processes/apps/programs:
    The FLipMouseGUI can run now in the tray, supporting a slot switch
    depending on the running programs.
    For this function, the tab "Slots" has the possibility to set
    a program (from the list of currently running programs) for
    each slot.
    Note: these settings are NOT stored on the FLipMouse, but in a JSON
2020-03-25 Added IR tab to HTML
2020-03-26 Changed delete all IR command to constant
2020-04-05 added some details about toolchain to Readme
2020-07-07 Bump electron from 5.0.12 to 7.2.4 in /webgui/src/fabi
    Bumps [electron](https://github.com/electron/electron) from 5.0.12 to 7.2.4.
    - [Release notes](https://github.com/electron/electron/releases)
    - [Changelog](https://github.com/electron/electron/blob/master/docs/breaking-changes.md)
    - [Commits](https://github.com/electron/electron/compare/v5.0.12...v7.2.4)
2020-07-26 Bump lodash from 4.17.15 to 4.17.19 in /webgui/src/flipmouse
    Bumps [lodash](https://github.com/lodash/lodash) from 4.17.15 to 4.17.19.
    - [Release notes](https://github.com/lodash/lodash/releases)
    - [Commits](https://github.com/lodash/lodash/compare/4.17.15...4.17.19)
2020-09-02 Bump bl from 3.0.0 to 3.0.1 in /webgui/src/fabi
    Bumps [bl](https://github.com/rvagg/bl) from 3.0.0 to 3.0.1.
    - [Release notes](https://github.com/rvagg/bl/releases)
    - [Commits](https://github.com/rvagg/bl/compare/v3.0.0...v3.0.1)
2020-10-28 Added version parser for local/available FM version, added tycmd update command.
2020-12-12 Bump ini from 1.3.5 to 1.3.8 in /webgui/src/fabi
    Bumps [ini](https://github.com/isaacs/ini) from 1.3.5 to 1.3.8.
    - [Release notes](https://github.com/isaacs/ini/releases)
    - [Commits](https://github.com/isaacs/ini/compare/v1.3.5...v1.3.8)
2021-01-13 Added download&upload of slot text files

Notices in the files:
hardware/FLipMouse/PCB/mainboard/FLipMouse3.kicad_pcb:
© AsTeRICS Foundation,2018
